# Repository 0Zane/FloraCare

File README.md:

# FloraCare

> Plant Tamagotchi — a connected device that monitors a plant's health using temperature, air humidity, soil moisture and light sensors. Built for the Trophées NSI 2026 (theme: Nature).

## 🎯 Goal

This project was created for the [Trophées NSI 2026](https://trophees-nsi.fr/) by @0Zane and @coderyansky. It offers a playful and educational experience: a digital companion that helps care for a plant by displaying real-time sensor data.

## 🏆 Awards

- **Regional Winner — Nature & Informatique**: FloraCare received the regional "Nature & Informatique" prize.
- **Nominated — Public Prize**: FloraCare was nominated for the Public Prize (see results).

See the official results: https://trophees-nsi.fr/resultats-2026

## 🧩 Hardware & Sensors

The project is based on a custom PCB driven by an **ESP32-S3**, chosen for native USB and enough power to run MicroPython.

| Component | Description | Interface / Protocol |
| :--- | :--- | :--- |
| **MCU** | ESP32-S3 Module | - |
| **PCB** | Custom design (Gerber files in `/hardware`) | - |
| **Display** | 1.9-inch 170x320 IPS color screen | **SPI** |
| **Temp / Humidity Sensor** | DHT22 | ADC |
| **Soil Moisture Sensor** | Analog soil moisture sensor | **ADC** |
| **Light Sensor** | BH1750 | **I2C** |
| **Power** | USB-C port | **5V DC -> 3.3V DC** |

> ⚡ The firmware runs on **MicroPython** and is intended to run continuously when powered via USB-C.

## 🚀 Quick Start

1. Flash MicroPython firmware to the ESP32-S3.
2. Copy all Python files to the microcontroller's flash.
3. Connect sensors to the pins defined in `main.py`.
4. Power via USB-C and observe readings on the display.

## 🌐 WiFi Web Interface

FloraCare creates a WiFi Access Point (AP) that serves a web interface to view plant data remotely.

### WiFi connection info

| Parameter | Value |
| :--- | :--- |
| **SSID** | `FloraCare` |
| **Password** | `pythonTNSI2026` |
| **IP Address** | `192.168.4.1` |
| **Protocol** | **HTTP** (port 80) |

### Accessing the web interface

1. Connect your device (phone, tablet, PC) to the `FloraCare` WiFi network.
2. Use the password `pythonTNSI2026`.
3. Open a browser and go to `http://192.168.4.1`.
4. The web page shows real-time sensor values (temperature, humidity, light, soil moisture).

> 💡 Tip: the web interface is available while the ESP32-S3 is powered via USB-C.

## 📁 Repository Structure

- `src/`: MicroPython code (main, libraries, config)
- `hardware/`: Gerber and PCB files (KiCad)
- `README.md`: project documentation and user guide
- `presentation.md`: project presentation
- `requirements.txt`: required libraries
- `LICENSE`: GPL v3

## 🤝 Contributing

This project is open source and open hardware. Contributions are welcome.
## 📝 License

This project is licensed under **GPL v3**. See the `LICENSE` file for details.

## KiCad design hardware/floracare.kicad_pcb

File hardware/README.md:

# PCB FloraCare

## 📋 Description

This is the printed circuit board (PCB) for the FloraCare project, designed to control and monitor plant growing conditions.

## 🛠 Design

* **Design Tool**: KiCad
* **Design Files**:

  * `floracare.kicad_sch` - Electrical schematic
  * `floracare.kicad_pcb` - PCB layout
  * `floracare.kicad_pro` - KiCad project file

## 📐 PCB Preview

View the PCB rendering:

## 📄 Electrical Schematic

For detailed PCB documentation, see: [floracare.pdf](floracare.pdf)

## 🏭 Manufacturing

The PCB was ordered from **JLCPCB** for fabrication.
Assembly is done by hand by @0Zane.

* **Manufacturer**: JLCPCB
* **Export Format**: Gerber files + drill files

## 📦 Directory Structure

```text
hardware/
├── floracare.kicad_sch       # Electrical schematic
├── floracare.kicad_pcb       # PCB design
├── floracare.kicad_pro       # Project file
├── pcb.png                   # PCB preview
├── floracare.pdf             # Complete documentation
└── README.md                 # This file
```

## 🔧 Required Tools

To view or modify this PCB project, you will need:

* **KiCad** 9.0 (https://www.kicad.org)

---

For any questions regarding the PCB or its manufacturing process, please open a discussion in the GitHub repository's Discussions section.

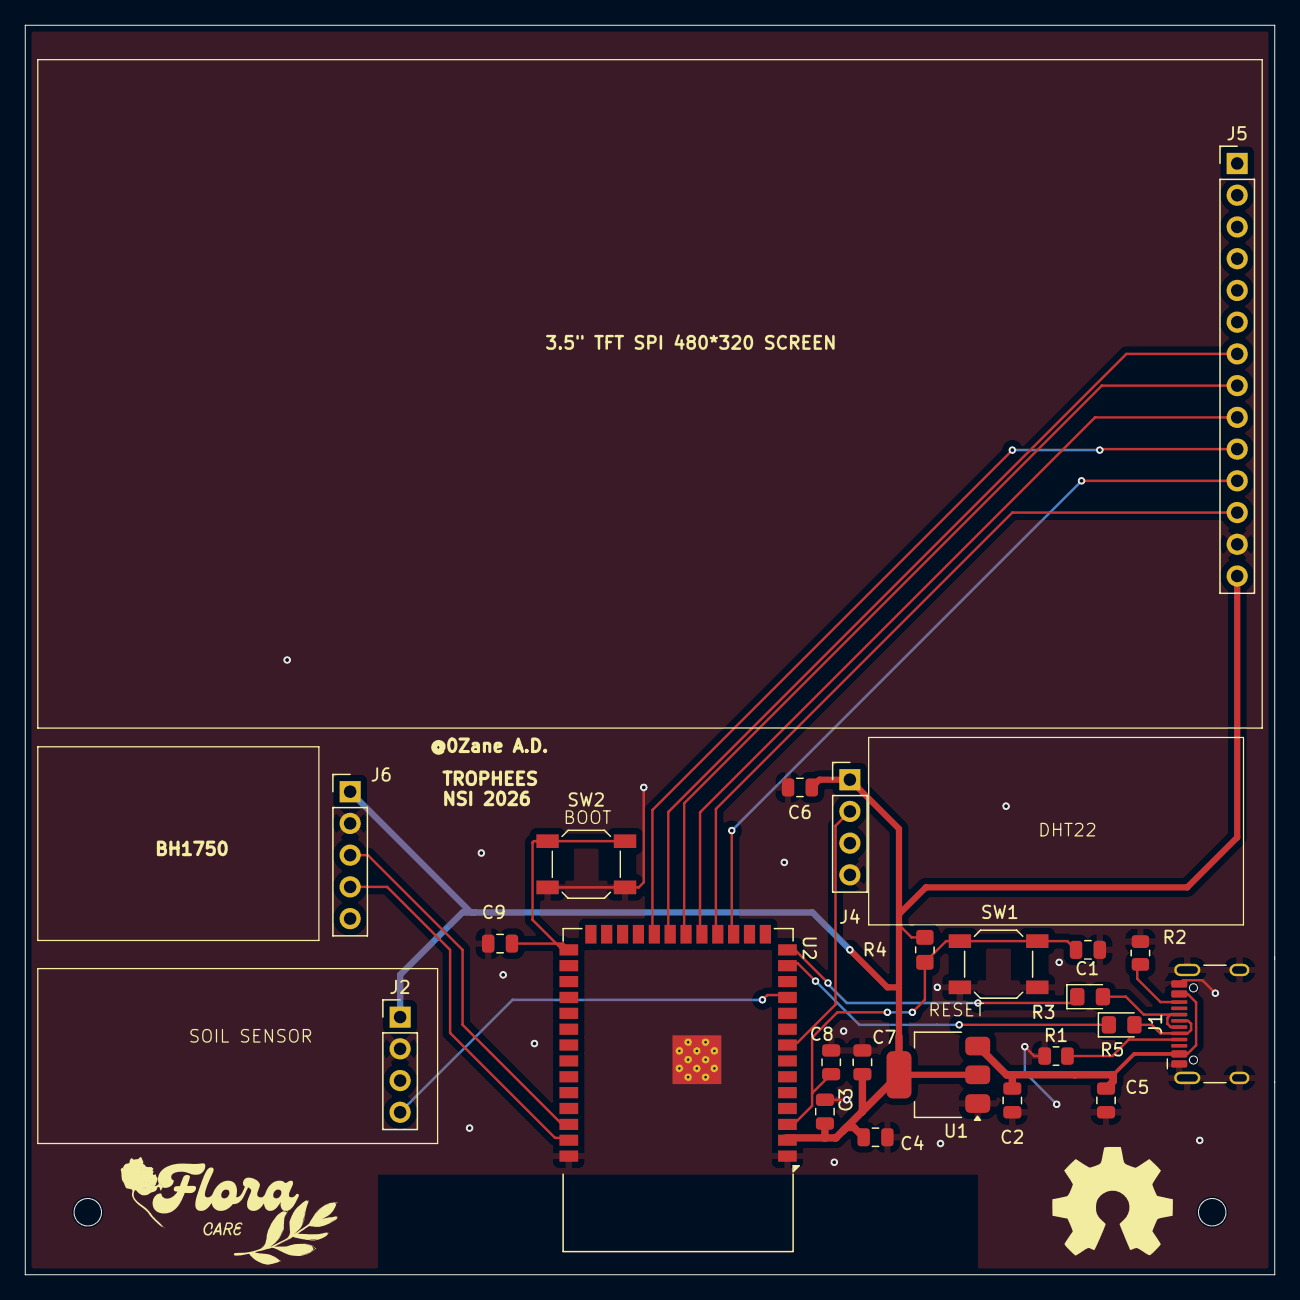
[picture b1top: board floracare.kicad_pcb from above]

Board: 2 copper layers, 100.0 x 100.0 mm, 23 parts (0 on the bottom side), 21 nets.

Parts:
C1, C3, C6, C8, C9: 0.1uF; C_0805_2012Metric
C2: 10uF; C_0805_2012Metric
C4, C7: 22uF; C_0805_2012Metric
C5: 10nF; C_0805_2012Metric
J1: USB_C_Receptacle_USB2.0_16P; USB_C_Receptacle_HCTL_HC-TYPE-C-16P-01A
J2, J4: Conn_01x04_Socket; PinHeader_1x04_P2.54mm_Vertical
J5: Conn_01x14_Socket; PinHeader_1x14_P2.54mm_Vertical
J6: Conn_01x05_Socket; PinHeader_1x05_P2.54mm_Vertical
R1, R2: 5.1K; R_0805_2012Metric
R3, R5: 22; LED_0805_2012Metric_Pad1.15x1.40mm_HandSolder
R4: 10k; R_0805_2012Metric_Pad1.20x1.40mm_HandSolder
SW1, SW2: SW_Push; SW_SPST_SKQG_WithStem
U1: AMS1117-3.3; SOT-223-3_TabPin2
U2: ESP32-S3-WROOM-1

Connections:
+3V3: C3.2, C4.1, C6.1, C7.1, J2.1, J4.1, J5.14, J6.1, R4.2, U1.2 (VO), U2.2 (3V3)
+5V: C2.2, C5.1, J1.A4 (VBUS), J1.A9 (VBUS), J1.B4 (VBUS), J1.B9 (VBUS), U1.3 (VI)
AO_SOIL: J2.4, U2.11 (IO18)
BOOT: C9.2, SW2.1, U2.27 (IO0)
CS: J5.12, U2.18 (IO10)
DATA+: J1.A6 (D+), J1.B6 (D+), R3.2
DATA-: J1.A7 (D-), J1.B7 (D-), R5.2
DC: J5.10, U2.22 (IO14)
DHT11: J4.2, U2.8 (IO15)
GND: C1.2, C2.1, C3.1, C4.2, C5.2, C6.2, C7.2, C8.2, C9.1, J1.A1 (GND), J1.A12 (GND), J1.B1 (GND), J1.B12 (GND), J1.S1 (SHIELD), J2.2, J4.4, J5.13, J6.2, R1.1, R2.2, SW1.2, SW2.2, U1.1 (GND), U2.1 (GND), U2.40 (GND), U2.41 (GND)
LED: J5.7, U2.21 (IO13)
LIGHT_SDA: J6.4, U2.39 (IO1)
LIGH_SCL: J6.3, U2.38 (IO2)
MOSI: J5.9, U2.19 (IO11)
unnamed: J1.A5 (CC1), R1.2
unnamed: J1.B5 (CC2), R2.1
unnamed: R3.1, U2.14 (USB_D+)
unnamed: R5.1, U2.13 (USB_D-)
RES: J5.11, U2.17 (IO9)
RESET: C1.1, C8.1, R4.1, SW1.1, U2.3 (EN)
SCLK: J5.8, U2.20 (IO12)

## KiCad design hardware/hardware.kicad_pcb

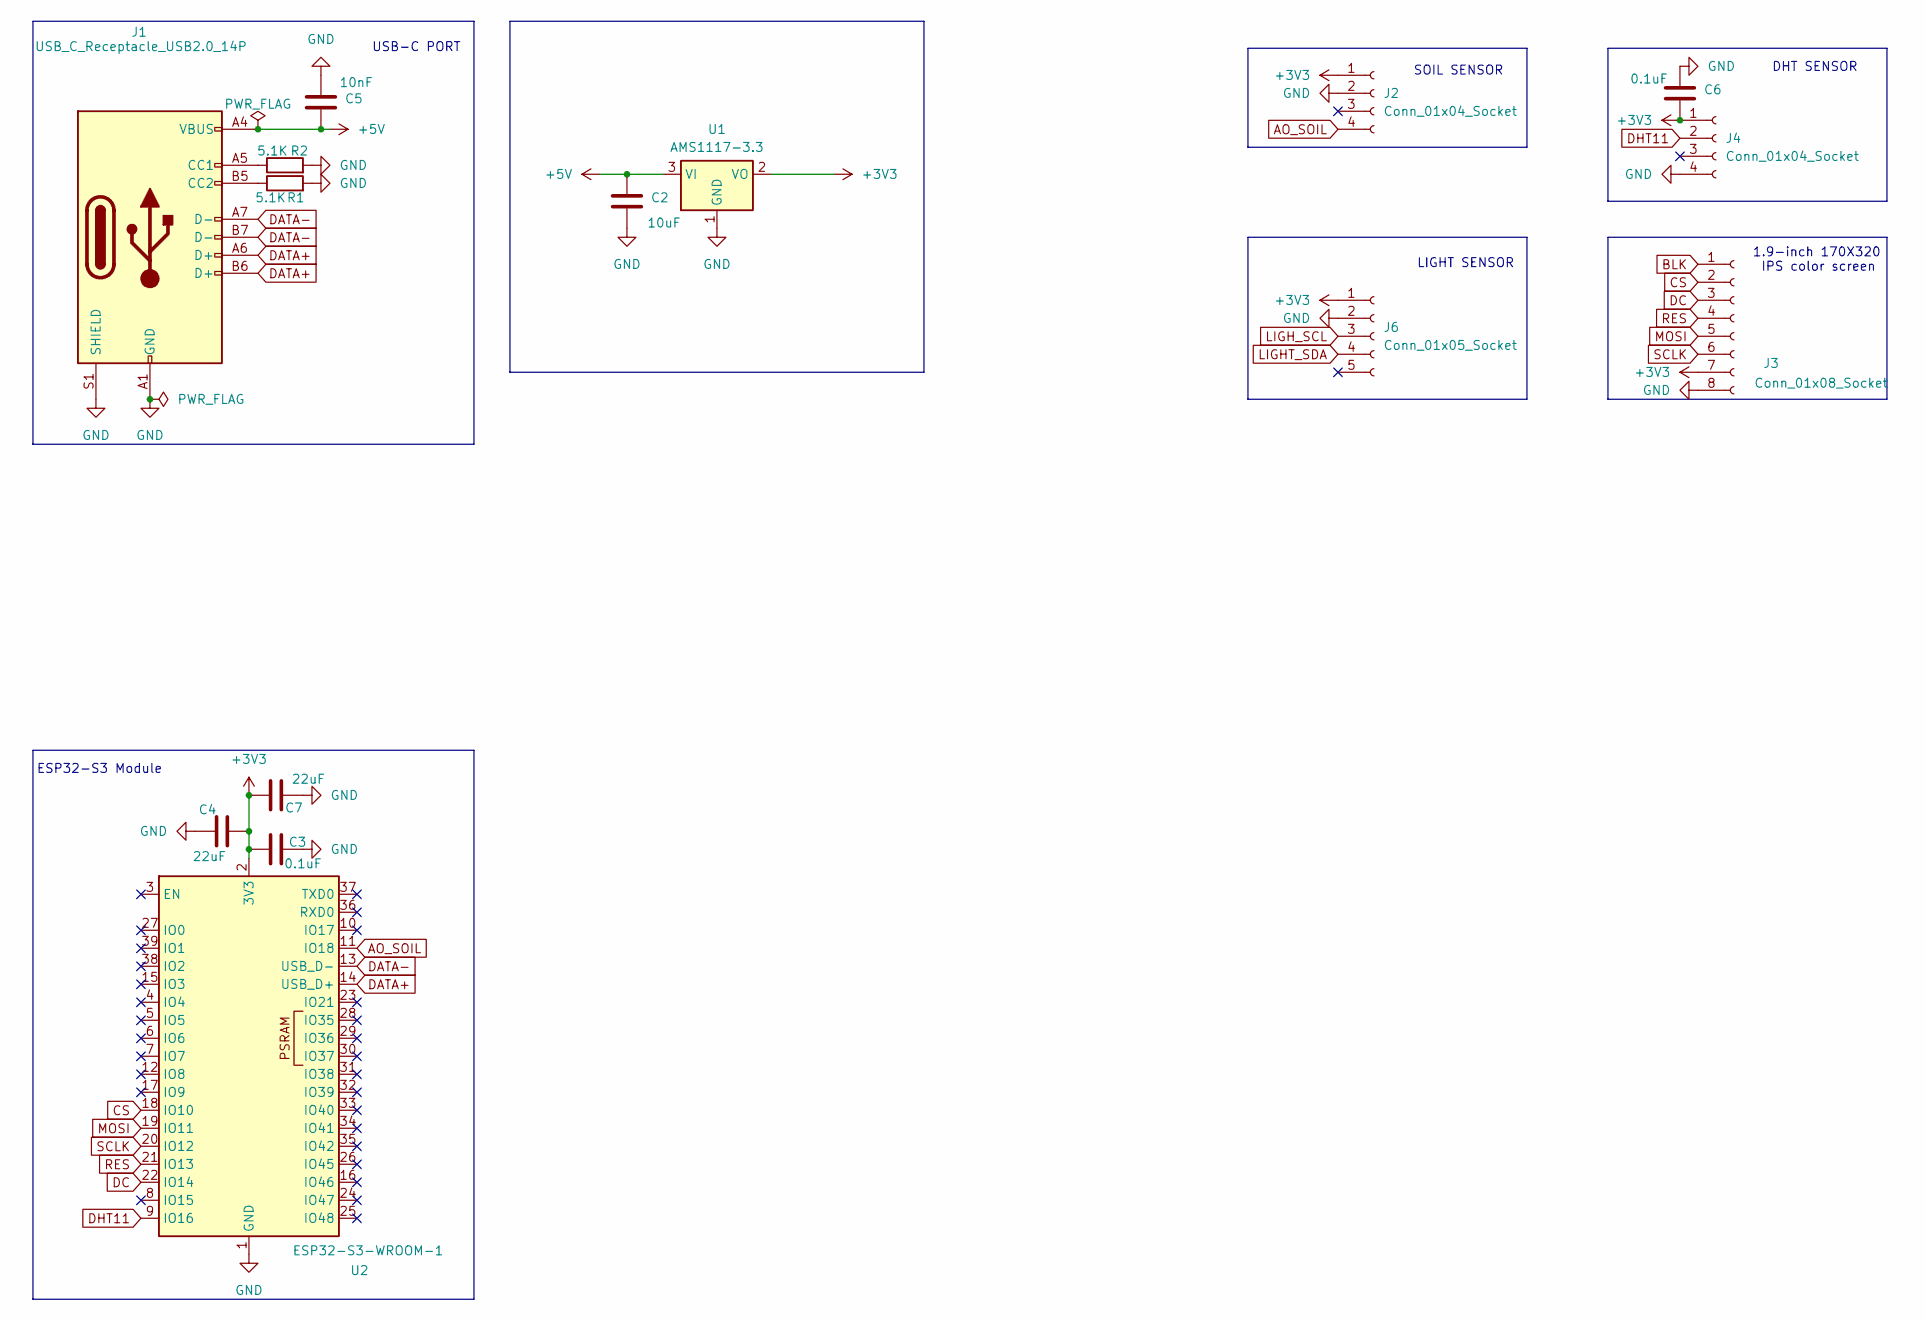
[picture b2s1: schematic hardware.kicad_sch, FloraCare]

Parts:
C2: 10uF; C_0805_2012Metric
C3, C6: 0.1uF; C_0805_2012Metric
C4, C7: 22uF; C_0805_2012Metric
C5: 10nF; C_0805_2012Metric
J1: USB_C_Receptacle_USB2.0_14P; USB_C_Receptacle_HRO_TYPE-C-31-M-12
J2, J4: Conn_01x04_Socket; PinHeader_1x04_P2.54mm_Vertical
J3: Conn_01x08_Socket; PinHeader_1x08_P2.54mm_Vertical
J6: Conn_01x05_Socket; PinHeader_1x05_P2.54mm_Vertical
R1, R2: 5.1K; R_0805_2012Metric
U1: AMS1117-3.3; SOT-223-3_TabPin2
U2: ESP32-S3-WROOM-1

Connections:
+3V3: C3.2, C4.1, C6.1, C7.1, J2.1, J3.7, J4.1, J6.1, U1.2 (VO), U2.2 (3V3)
+5V: C2.2, C5.1, J1.A4 (VBUS), J1.A9 (VBUS), J1.B4 (VBUS), J1.B9 (VBUS), U1.3 (VI)
AO_SOIL: J2.4, U2.11 (IO18)
BLK: J3.1
CS: J3.2, U2.18 (IO10)
DATA+: J1.A6 (D+), J1.B6 (D+), U2.14 (USB_D+)
DATA-: J1.A7 (D-), J1.B7 (D-), U2.13 (USB_D-)
DC: J3.3, U2.22 (IO14)
DHT11: J4.2, U2.9 (IO16)
GND: C2.1, C3.1, C4.2, C5.2, C6.2, C7.2, J1.A1 (GND), J1.A12 (GND), J1.B1 (GND), J1.B12 (GND), J1.S1 (SHIELD), J2.2, J3.8, J4.4, J6.2, R1.2, R2.2, U1.1 (GND), U2.1 (GND), U2.40 (GND), U2.41 (GND)
LIGHT_SDA: J6.4
LIGH_SCL: J6.3
MOSI: J3.5, U2.19 (IO11)
unnamed: J1.A5 (CC1), R2.1
unnamed: J1.B5 (CC2), R1.1
RES: J3.4, U2.21 (IO13)
SCLK: J3.6, U2.20 (IO12)

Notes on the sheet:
DHT SENSOR
SOIL SENSOR
LIGHT SENSOR
USB-C PORT
1.9-inch 170X320
IPS color screen
ESP32-S3 Module

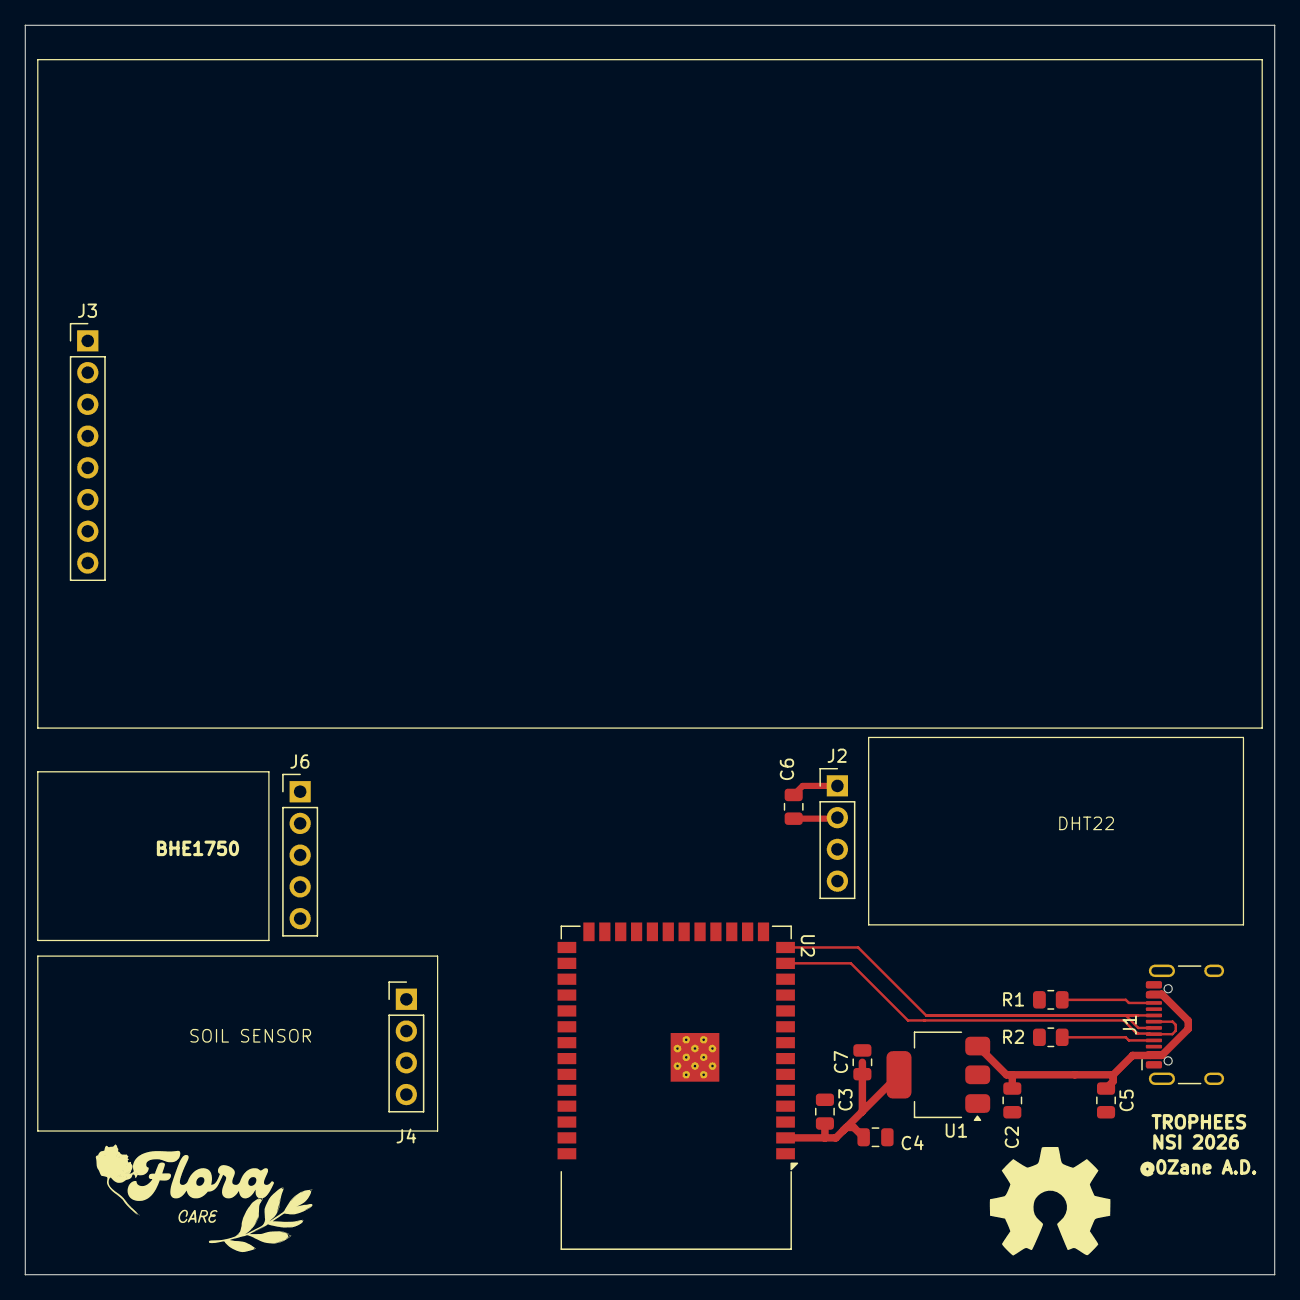
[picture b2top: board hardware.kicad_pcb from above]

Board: 2 copper layers, 100.0 x 100.0 mm, 15 parts (0 on the bottom side), 14 nets.

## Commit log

2026-02-20 Creating structure
2026-03-03 Update README with project description
    Added project description for TNSI.
2026-03-05 Expand README with hardware and components information
    Added detailed hardware and components section to README.
2026-03-06 Initial led blink setup for esp32 s3
    This is the first step of the project to understand micropython.
    This branche will only be merged to the maun branch when it will contain the real firmware code.
2026-03-06 Adding temp feature
    Adding temperature reading with DHT11 using dht library , and ON LED
2026-03-07 Updating REAME
2026-03-07 Adding hardware directory for PCB
2026-03-08 Adding usbc port
2026-03-09 Add esptool to requirements
2026-03-09 Add LICENSE file
2026-03-09 Change project license to GPL v3 in README.md
    Updated license information in README.md to specify GPL v3.
2026-03-10 Add description for the 1.9-inch color screen
    Updated the display description in the components table.
2026-03-11 Adding SPI pin socket
2026-03-11 [ERC GOOD] , correcting tag name MOSI & SCLk, Adding tags to ESP-32-S3
2026-03-11 Making PCB + screen route + switching CS and DC pins
2026-03-12 Adding AMS117 Voltage divider (NO CAPACITOR)
2026-03-12 Adding usbc routes [ERC NOT STABLE]
2026-03-12 Adding DHT sensor pins
2026-03-13 Add DHT22 sensor to README specifications
2026-03-14 Changing pins
2026-03-14 Adding soil sensor pins
2026-03-14 [ERC VERIFIED] Adding soil sensor pin
2026-03-14 Adding Soil sensor on PCB
2026-03-14 feat(sensor): add soil moisture reader on GPIO 18
    - Read analog soil moisture via ADC on GPIO 18
    - read_soil() returns raw u16 and moisture percentage (0-100%)
    - ATTN_11DB for 0-3.3V range; script runs in loop with 2s interval
    Made-with: Cursor
2026-03-14 Add hardware backup directory to .gitignore
2026-03-14 Update Footprint property for connectors in schematic
2026-03-14 Updating gitignore
2026-03-14 feat(display): show DHT11 and soil sensors on ST7789
    - Add display_sensor UI with cards, bars, incremental updates
    - Add 170x320 rotation table with xstart/ystart in driver
    - Clamp _set_window to valid range to fix edge corruption
    - main.py entry point runs display_sensor
2026-03-15 Rename project to FloraCare and update description
    Updated project name and description in README.
2026-03-15 Adding Light sensor pins on schematic
2026-03-15 Adding all capacitors
2026-03-15 Making first version of the PCB [NOT ROUTED ]
2026-03-15 Update README with sensor details and project description
2026-03-15 Removing message
2026-03-15 Adding visual assets to the project
2026-03-15 Add banner image to README
2026-03-15 Fix image syntax in README.md
2026-03-15 Placing silkscreen in better zones to preapare mounting holes
2026-03-15 Putting ground over the back of the PCB
2026-03-15 Revert "Merge branch 'feature/display-output' into main"
    This reverts commit b133c3eb0e3cd1f3bc46de7860bfc4a558904355, reversing
    changes made to 9a763ac953a70affe540ec869e4ab95926b2e80e.
2026-03-15 Remaking hardware directory
2026-03-15 Optimizing code with functions
2026-03-15 Repairing hardware repository [STABLE]
2026-03-15 Update global pcb
2026-03-16 Fixing size hole problem and mass plan [ ERC 9 ERRORS ]
2026-03-16 Adding vias
2026-03-17 Adding EN and BOOT buttons
2026-03-17 Fixing PCB + adding BOOT and RESET BUTTONS [DRC NOT STABLE]
2026-03-17 Updating general Project
2026-03-18 Adding 2 mounting holes
2026-03-18 Replacing usb slot
2026-03-18 feat: add ILI9488 display driver
    Based on Kevin G. Schlosser's implementation (Copyright 2024-2025).
    Includes LVGL-compatible wrapper, initialization sequence, and raw SPI driver
    without external framework dependencies. Also adds lcd_bus type stubs.
2026-03-18 Rounting UCBC 8 pin
2026-03-18 chore: update comments
    chore: update comments
2026-03-19 Finishing PCB , [USBC NOT STABLE WITH DRC]
2026-03-19 Finishing USB-C Routing & PCB [DRC STABLE]
2026-03-19 Repacing silk [Warnings Fixed on DRC except1 ]
2026-03-19 Fixing ESP32 -S3 WRROM1 MODULE Warning [DRC 100% STABLE]
2026-03-19 Adding mounting holes
2026-03-19 Correcting details
2026-03-19 Update DHT_PIN and add LIGHT_SCL/LIGHT_SDA
2026-03-19 Define sensor and screen pin constants
    Added constants for sensor and screen pins, and improved comments.
2026-03-20 feat: add BH1750 light sensor and switch DHT11 to DHT22
2026-03-20 Uploading PCB images
2026-03-20 Renaming file
2026-03-20 Adding readme for hardware
2026-03-20 Add dht to requirements
2026-03-21 Creating access point function
2026-03-21 Adding exception handling
2026-03-21 Correcting bug and handling error
2026-03-21 Replacing wifi launch
2026-03-21 Correcting spelling mistake on launch function
2026-03-21 Adding password for Wifi
2026-03-21 Replacing WIFI parameters as variables
2026-03-21 Optimizing WIFI code structure
2026-03-21 Using Claude , creating Webpage for floracare
2026-03-21 Adding informations on WIFI AP + web interface
2026-03-21 Adding server hosted by ESP Device
2026-03-21 Correcting quotes problem
2026-03-21 Adding requirements
2026-03-22 chore: remove ili9488_raw, move stubs
2026-03-22 Adding comments for more code visibility
2026-03-22 Translating text
2026-03-22 Updating javascript
2026-03-22 Fixing Data POST by adding JSON.stringify in the body
2026-03-22 Creating HTTP server
2026-03-22 feat: add animated robot face driver for ILI9488 480x320 display
2026-03-23 Creating presentation.md page
2026-03-24 Making a variable for maxpacket size
2026-03-24 Remove 3D printed case details from README
    Removed the 3D printed case information from the README.
2026-03-24 Correcting pin during PCB test
2026-03-25 Defining variables for plant stats
2026-03-25 Adding soil moisture in webpage
2026-03-25 Defining plants dictionnaries
2026-03-25 Adding plant state variables
2026-03-25 Adding plant statistic handler
2026-03-25 Understanding string received on POST HTTP to associate to a plant model from dictionnary
2026-03-25 Correcting pin
2026-03-25 Removing light analisis to let the main code calculate the average
2026-03-25 Making light data algorithm
2026-03-25 Correcting variable definition bug
2026-03-26 Implement feedback messages for plant care states
    Added print statements for plant care conditions based on temperature, moisture, humidity, and light levels.
2026-03-26 Update main.py
    Removing light excess detection
2026-03-26 remove(display): drop LVGL-based ILI9488 driver and init module
    Replaced by a custom MicroPython SPI driver that requires no LVGL
    or lcd_bus dependencies.
2026-03-26 refactor(display): redesign Face with StatusBar, batch SPI, and no pupils
    - Remove drifting pupil animation; eyes are now solid rounded rectangles
    - Add StatusBar class: draws TEMP/HUM/SOIL/LUX strip below a neon separator
    - Batch eye rows in groups of 8 to reduce SPI transaction overhead
    - Double SPI baudrate to 40 MHz and fix MADCTL for correct landscape orientation
    - Rate-limit blink animation with _BSTEP_MS instead of blocking sleep_ms
    - Add restore_dc() on Display to reclaim GPIO 15 after DHT22 use
2026-03-26 refactor(main): integrate Face, non-blocking sensor loop, cleanup
    - Instantiate Face at boot and call face.update() on every loop iteration
    - Schedule sensor reads every 2 s with ticks_ms instead of blocking sleep
    - Call face.lcd.restore_dc() after each DHT22 read to reclaim GPIO 15
    - Push sensor readings to face.set_sensors() for StatusBar display
    - Fix light average accumulation (reset lum_sum on period rollover)
    - Clean up comments, align constants, translate log messages to English
2026-03-26 fix(main): add 2s timeout on socket recv to prevent hang on stalled connections
2026-03-26 Defining missing variable
2026-03-26 Reducing Moist tolerance
2026-03-26 fix(main): restore plant state debug prints, screen pin constants, and f-strings
2026-03-26 Changing task attribution format
2026-03-26 Correcting soil algorithm
2026-03-26 Elarging moist tolerance
2026-03-26 chore: remove built-in MicroPython modules from requirements
2026-03-26 feat(anims): add AngryAnim — red eyes with diagonal brow cutoff and blink
2026-03-26 chore: add .DS_Store to gitignore
2026-03-26 feat(main): integrate animation system with IdleAnim and AngryAnim
2026-03-26 refactor(face): replace inline blink logic with pluggable animation system
2026-03-26 fix(angry): flip brow direction (inner corner deepest), remove blink, add sad mouth
2026-03-27 chore: add Makefile for dev/deploy shortcuts
2026-03-27 Adding picture of pcb physical
2026-03-28 fix(display): correct DC and MISO pin numbers to GPIO 14
    _DC was set to 15 (wrong), now matches the hardware schematic (GPIO 14).
    MISO hardcoded literal replaced with _MISO constant.
    Removed stale DISPLAY_DC comment from main.py.
2026-03-28 fix(display): rotate ILI9488 output by 180 degrees
    Set MADCTL to the 180-degree landscape orientation so the face UI renders upright for inverted physical mounting.
2026-03-28 Adding final project image
2026-03-29 feat(display): highlight out-of-range sensor values in red
    Sensor readings that fall outside plant tolerance thresholds
    now render in red instead of cyan on the status bar.
2026-04-01 Adding graptosedum plant model
2026-04-12 Adding graptosedum
2026-06-09 Translating documentation to english
2026-06-25 Translating hardware README.md from French to English
